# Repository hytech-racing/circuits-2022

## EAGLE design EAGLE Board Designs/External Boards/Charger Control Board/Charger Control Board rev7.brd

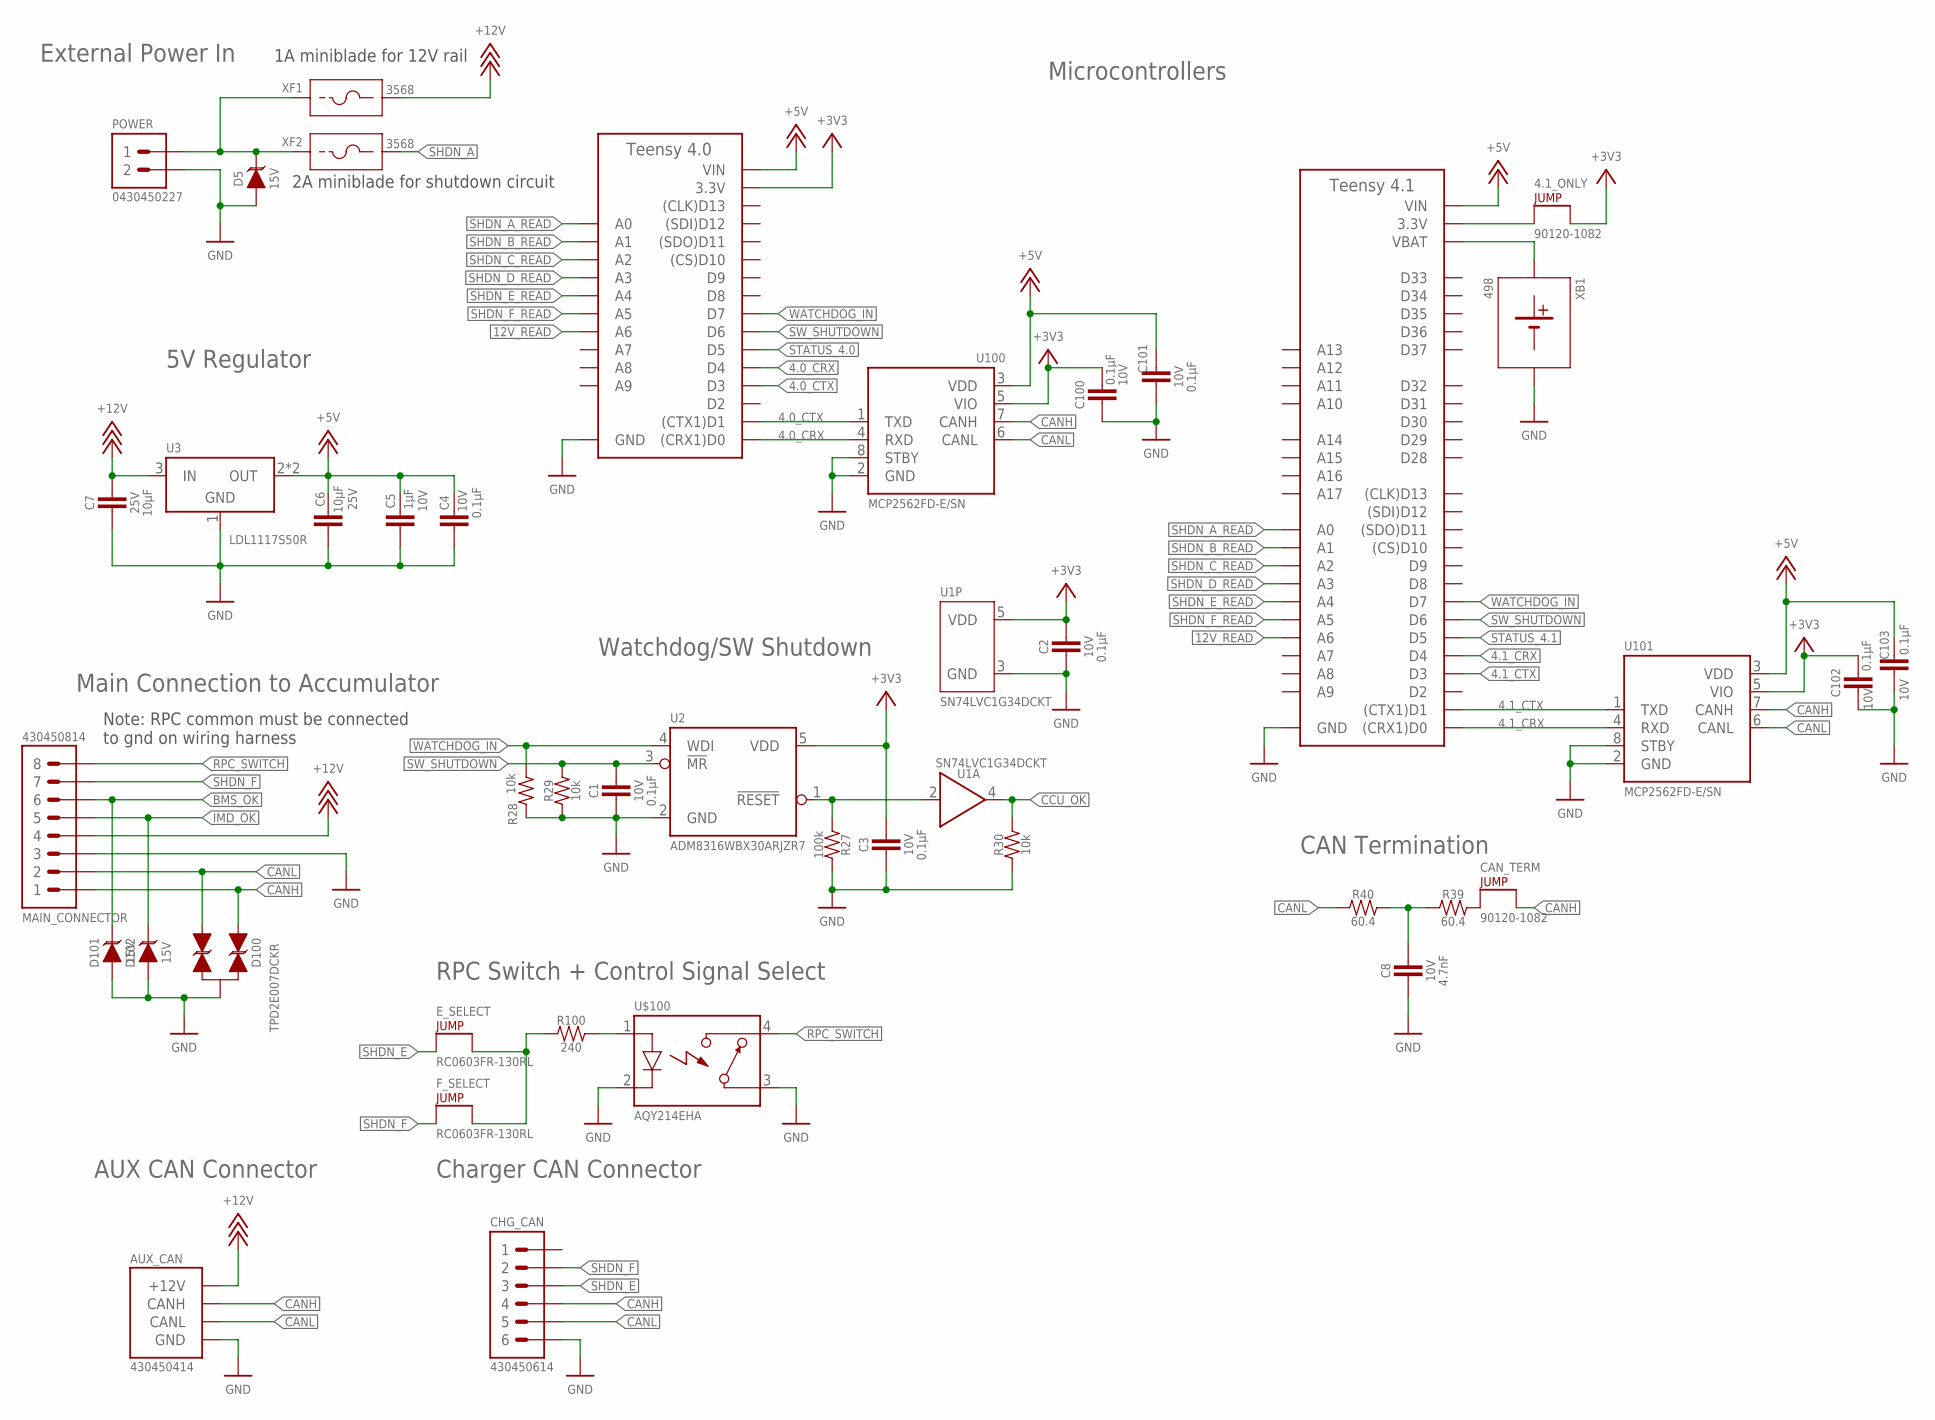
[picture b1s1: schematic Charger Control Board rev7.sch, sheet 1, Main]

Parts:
4.1_ONLY: JUMPER__1X02; 1X02
A1: TEENSY_4.1; TEENSY_LONG_EXT
A2: TEENSY_4.0; TEENSY_SHORT
AUX_CAN: CONNECTOR-CAN_MF_T_V_; MOLEX_MICROFIT_PTH_VERTICAL_04_DUAL
C1, C2, C3, C4, C100, C101, C102, C103: CAPACITOR_0603_10V_0.1UF; 0603-CAP
C5: CAPACITOR_0603_10V_1UF; 0603-CAP
C6, C7: CAPACITOR_0603_25V_10UF; 0603-CAP
C8: CAPACITOR_0603_10V_4.7NF; 0603-CAP
CAN_TERM: JUMPER__1X02; 1X02
CHG_CAN: CONNECTOR-6_MF_T_V_; MOLEX_MICROFIT_PTH_VERTICAL_06_DUAL
D5, D101, D102: TVS_15V; SOT-23
D100: TVS_BIDIRECTIONAL_DUAL; SC-70-3
E_SELECT: JUMPER_0603_; 0603-RES
F_SELECT: JUMPER_0603_; 0603-RES
MAIN_CONNECTOR: CONNECTOR-8_MF_T_V_; MOLEX_MICROFIT_PTH_VERTICAL_08_DUAL
POWER: CONNECTOR-2_μF_T_V_; MOLEX_MICROFIT_PTH_VERTICAL_02_DUAL
R27: RESISTOR_0603_100K; 0603-RES
R28, R29, R30: RESISTOR_0603_10K; 0603-RES
R39, R40: RESISTOR_0603_60.4; 0603-RES
R100: RESISTOR_0603_240; 0603-RES
U1: LOGICGATE_BUFFER; SC-70-5
U2: ADM8316WBX30; SOT-23-5
U3: VOLTAGE_REGULATOR_SOT-223_5V; SOT-223
U100, U101: MCP2562FD; SOIC-08(NARROW,0.15")
U$100: RELAY_SOLIDSTATE_NO; DIP-4
XB1: BATTERY_HOLDER_KEYSTONE_498; 498
XF1, XF2: FUSE_HOLDER_MINIBLADEPTH; 3568

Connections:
4.0_CRX: A2.D0 ((CRX1)D0), A2.D4, U100.4 (RXD)
4.0_CTX: A2.D1 ((CTX1)D1), A2.D3, U100.1 (TXD)
4.1_CRX: A1.D0 ((CRX1)D0), A1.D4, U101.4 (RXD)
4.1_CTX: A1.D1 ((CTX1)D1), A1.D3, U101.1 (TXD)
12V_READ: A1.D20 (A6), A2.D20 (A6); also elsewhere on the board
+3V3: 4.1_ONLY.2, A2.3.3V, C2.2, C3.2, C100.2, C102.2, U1.5 (VDD), U2.5 (VDD), U100.5 (VIO), U101.5 (VIO); also elsewhere on the board
+5V: A1.VIN, A2.VIN, C4.2, C5.1, C6.1, C101.2, C103.2, U3.2 (OUT), U3.4 (OUT), U100.3 (VDD), U101.3 (VDD); also elsewhere on the board
+12V: AUX_CAN.1 (+12V), C7.1, MAIN_CONNECTOR.4, U3.3 (IN), XF1.3 (2), XF1.4 (2); also elsewhere on the board
BMS_OK: D101.3 (C), MAIN_CONNECTOR.6; also elsewhere on the board
CANH: AUX_CAN.4 (CANH), CAN_TERM.2, CHG_CAN.4, D100.1 (C1), MAIN_CONNECTOR.1, U100.7 (CANH), U101.7 (CANH)
CANL: AUX_CAN.3 (CANL), CHG_CAN.5, D100.2 (C2), MAIN_CONNECTOR.2, R40.1, U100.6 (CANL), U101.6 (CANL)
CCU_OK: R30.2, U1.4 (OUT); also elsewhere on the board
GND: A1.AGND/GND (GND), A1.GND, A1.GND@2 (GND), A2.AGND/GND (GND), A2.GND, AUX_CAN.2 (GND), C1.1, C2.1, C3.1, C4.1, C5.2, C6.2, C7.2, C8.2, C100.1, C101.1, C102.1, C103.1, CHG_CAN.6, D5.1 (A), D100.3 (A), D101.1 (A), D102.1 (A), MAIN_CONNECTOR.3, POWER.2, R27.2, R28.2, R29.1, R30.1, U1.3 (GND), U2.2 (GND), U3.1 (GND), U100.2 (GND), U100.8 (STBY), U101.2 (GND), U101.8 (STBY), U$100.2 (CONTROL-), U$100.3 (CONTACT1), XB1.2 (MINUS); also elsewhere on the board
IMD_OK: D102.3 (C), MAIN_CONNECTOR.5; also elsewhere on the board
unnamed: D5.3 (C), POWER.1, XF1.1, XF1.2 (1), XF2.1, XF2.2 (1)
unnamed: R27.1, U1.2 (IN), U2.1 (!RESET!)
unnamed: CAN_TERM.1, R39.2
unnamed: E_SELECT.2, F_SELECT.2, R100.1
unnamed: A1.VBAT, XB1.1 (PLUS)
unnamed: C8.1, R39.1, R40.2
unnamed: R100.2, U$100.1 (CONTROL+)
unnamed: 4.1_ONLY.1, A1.3V3 (3.3V), A1.3V3@2 (3.3V), A1.3V3@3 (3.3V)
RPC_SWITCH: MAIN_CONNECTOR.8, U$100.4 (CONTACT2)
SHDN_A: XF2.3 (2), XF2.4 (2); also elsewhere on the board
SHDN_A_READ: A1.D14 (A0), A2.D14 (A0); also elsewhere on the board
SHDN_B_READ: A1.D15 (A1), A2.D15 (A1); also elsewhere on the board
SHDN_C_READ: A1.D16 (A2), A2.D16 (A2); also elsewhere on the board
SHDN_D_READ: A1.D17 (A3), A2.D17 (A3); also elsewhere on the board
SHDN_E: CHG_CAN.3, E_SELECT.1; also elsewhere on the board
SHDN_E_READ: A1.D18 (A4), A2.D18 (A4); also elsewhere on the board
SHDN_F: CHG_CAN.1, CHG_CAN.2, F_SELECT.1, MAIN_CONNECTOR.7; also elsewhere on the board
SHDN_F_READ: A1.D19 (A5), A2.D19 (A5); also elsewhere on the board
STATUS_4.0: A2.D5; also elsewhere on the board
STATUS_4.1: A1.D5; also elsewhere on the board
SW_SHUTDOWN: A1.D6, A2.D6, C1.2, R29.2, U2.3 (!MR!)
WATCHDOG_IN: A1.D7, A2.D7, R28.1, U2.4 (WDI)

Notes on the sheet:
External Power In
5V Regulator
Main Connection to Accumulator
CAN Termination
Microcontrollers
Watchdog/SW Shutdown
Charger CAN Connector
AUX CAN Connector
1A miniblade for 12V rail
2A miniblade for shutdown circuit
RPC Switch + Control Signal Select
Note: RPC common must be connected to gnd on wiring harness

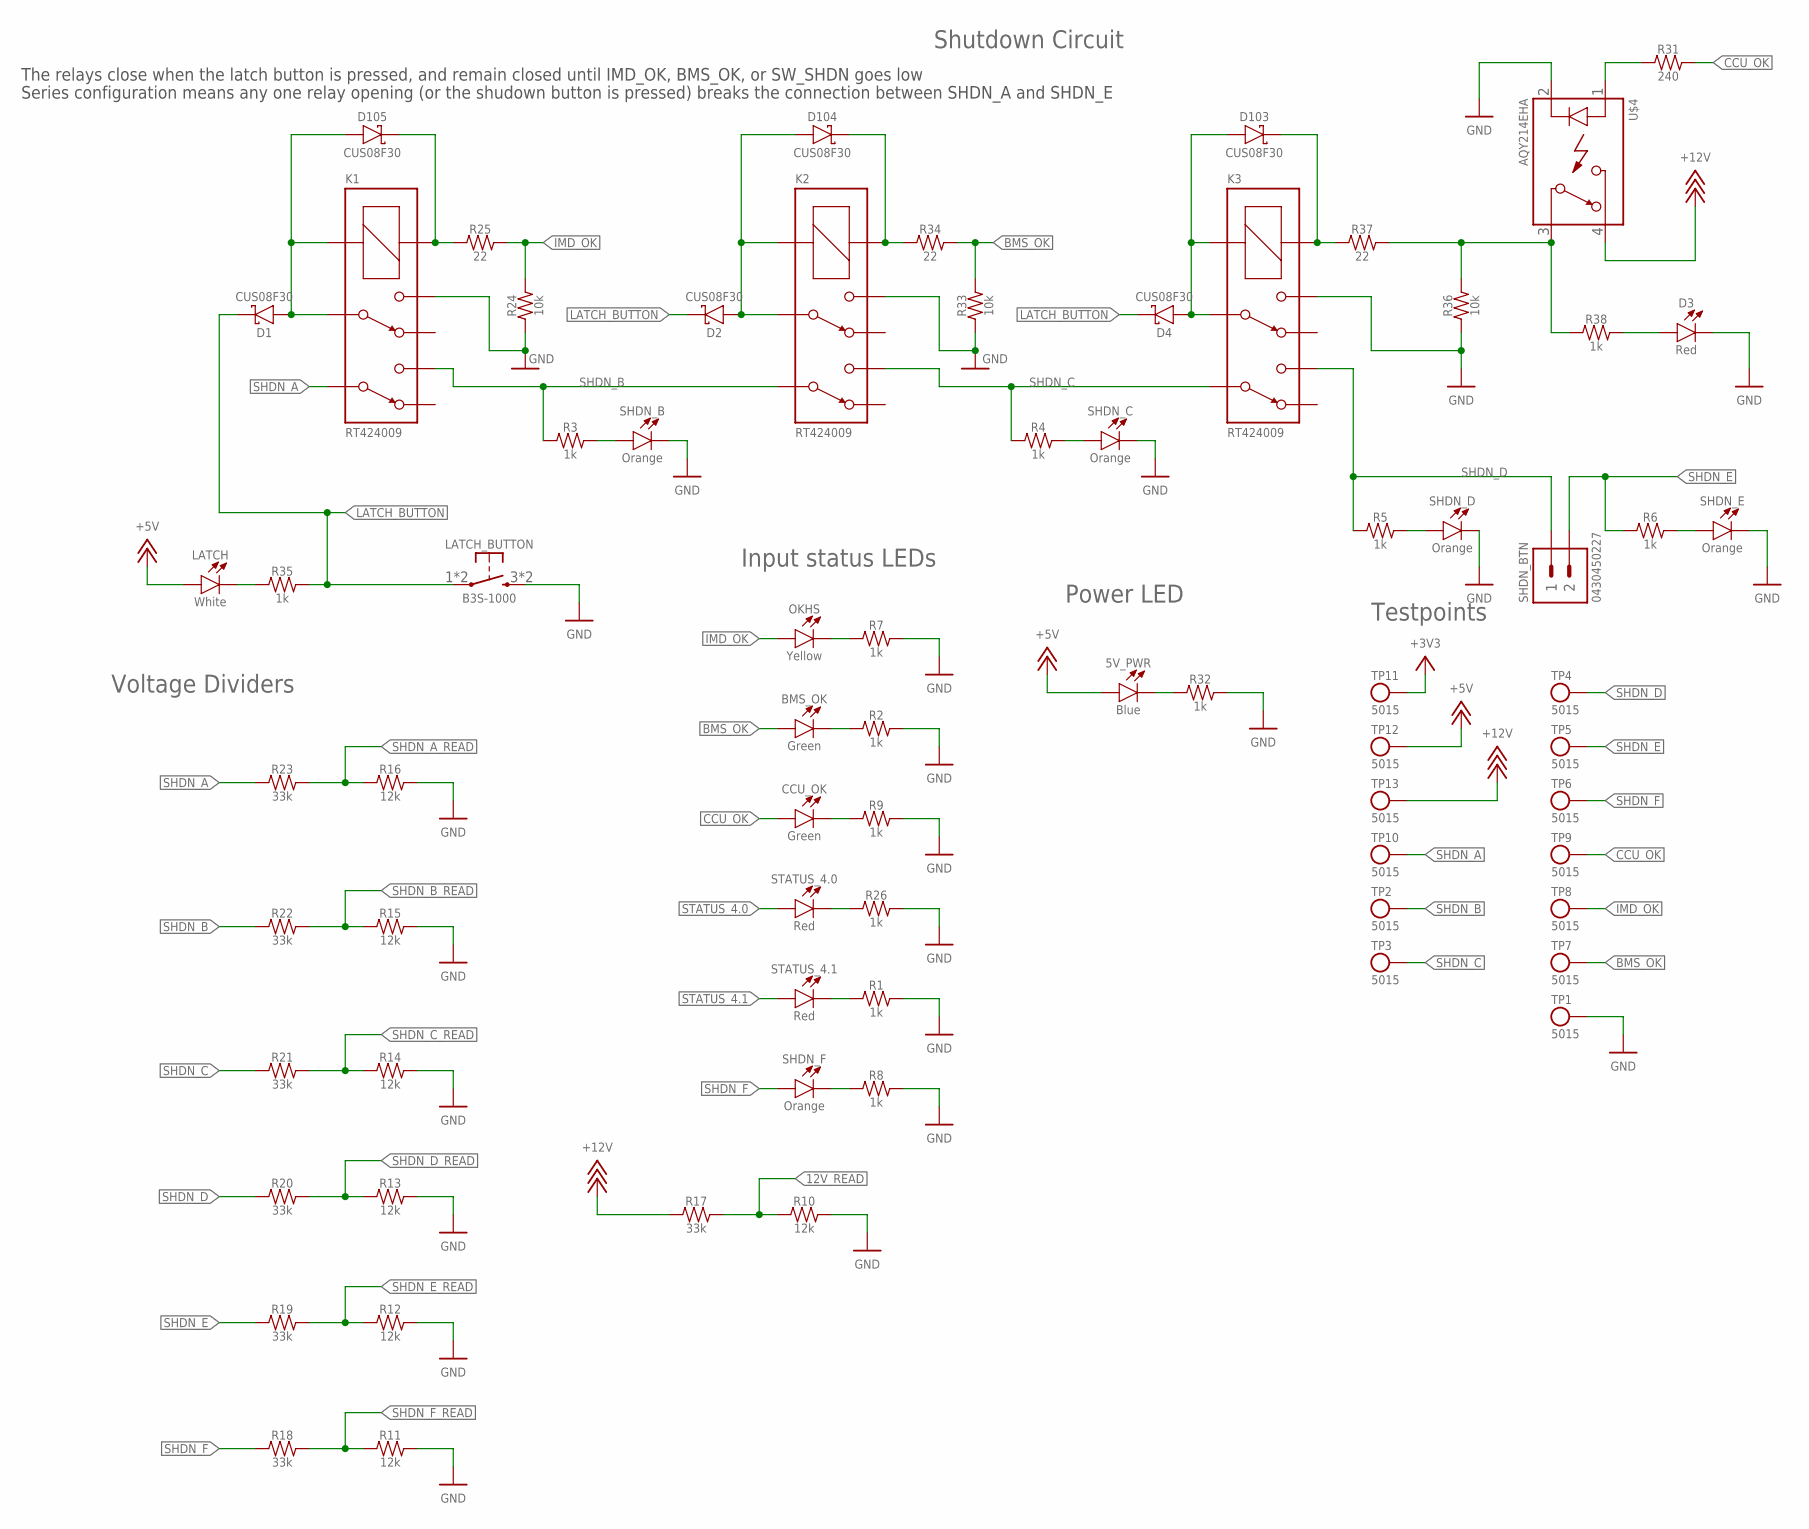
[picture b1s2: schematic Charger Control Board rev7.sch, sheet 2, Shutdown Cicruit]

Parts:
5V_PWR: LED_0603_BLUE; 0603-LED
BMS_OK: LED_0603_GREEN; 0603-LED
CCU_OK: LED_0603_GREEN; 0603-LED
D1, D2, D4, D103, D104, D105: SCHOTTKY_SOD323_30V; SOD-323
D3: LED_0603_RED; 0603-LED
K1, K2, K3: RELAY_DPDT; RT*2*
LATCH: LED_0603_WHITE; 0603-LED
LATCH_BUTTON: BUTTON; B3S-100X
OKHS: LED_0603_YELLOW; 0603-LED
R1, R2, R3, R4, R5, R6, R7, R8, R9, R26, R32, R35, R38: RESISTOR_0603_1K; 0603-RES
R10, R11, R12, R13, R14, R15, R16: RESISTOR_0603_12K; 0603-RES
R17, R18, R19, R20, R21, R22, R23: RESISTOR_0603_33K; 0603-RES
R24, R33, R36: RESISTOR_0603_10K; 0603-RES
R25, R34, R37: RESISTOR_0603_22; 0603-RES
R31: RESISTOR_0603_240; 0603-RES
SHDN_B: LED_0603_ORANGE; 0603-LED
SHDN_BTN: CONNECTOR-2_μF_T_V_; MOLEX_MICROFIT_PTH_VERTICAL_02_DUAL
SHDN_C: LED_0603_ORANGE; 0603-LED
SHDN_D: LED_0603_ORANGE; 0603-LED
SHDN_E: LED_0603_ORANGE; 0603-LED
SHDN_F: LED_0603_ORANGE; 0603-LED
STATUS_4.0, STATUS_4.1: LED_0603_RED; 0603-LED
TP1, TP2, TP3, TP4, TP5, TP6, TP7, TP8, TP9, TP10, TP11, TP12, TP13: TEST_POINT; 5015
U$4: RELAY_SOLIDSTATE_NO; DIP-4

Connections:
12V_READ: R10.1, R17.2; also elsewhere on the board
+3V3: TP11.1; also elsewhere on the board
+5V: 5V_PWR.2 (A), LATCH.2 (A), TP12.1; also elsewhere on the board
+12V: R17.1, TP13.1, U$4.4 (CONTACT2); also elsewhere on the board
BMS_OK: BMS_OK.2 (A), R33.2, R34.2, TP7.1; also elsewhere on the board
CCU_OK: CCU_OK.2 (A), R31.2, TP9.1; also elsewhere on the board
GND: D3.1 (C), K1.14 (4), K2.14 (4), K3.14 (4), LATCH_BUTTON.3 (S), LATCH_BUTTON.4 (S), R1.2, R2.2, R7.2, R8.2, R9.2, R10.2, R11.2, R12.2, R13.2, R14.2, R15.2, R16.2, R24.1, R26.2, R32.2, R33.1, R36.1, SHDN_B.1 (C), SHDN_C.1 (C), SHDN_D.1 (C), SHDN_E.1 (C), TP1.1, U$4.2 (CONTROL-); also elsewhere on the board
IMD_OK: OKHS.2 (A), R24.2, R25.2, TP8.1; also elsewhere on the board
LATCH_BUTTON: D1.C, D2.C, D4.C, LATCH_BUTTON.1, LATCH_BUTTON.2, R35.2
unnamed: R8.1, SHDN_F.1 (C)
unnamed: R31.1, U$4.1 (CONTROL+)
unnamed: D1.A, D105.A, K1.11 (3), K1.A2 (COIL-)
unnamed: D105.C, K1.A1 (COIL+), R25.1
unnamed: D104.C, K2.A1 (COIL+), R34.1
unnamed: D2.A, D104.A, K2.11 (3), K2.A2 (COIL-)
unnamed: D103.C, K3.A1 (COIL+), R37.1
unnamed: R36.2, R37.2, R38.1, U$4.3 (CONTACT1)
unnamed: LATCH.1 (C), R35.1
unnamed: R5.2, SHDN_D.2 (A)
unnamed: R6.2, SHDN_E.2 (A)
unnamed: D4.A, D103.A, K3.11 (3), K3.A2 (COIL-)
unnamed: D3.2 (A), R38.2
unnamed: R4.2, SHDN_C.2 (A)
unnamed: R3.2, SHDN_B.2 (A)
unnamed: OKHS.1 (C), R7.1
unnamed: BMS_OK.1 (C), R2.1
unnamed: CCU_OK.1 (C), R9.1
unnamed: R26.1, STATUS_4.0.1 (C)
unnamed: 5V_PWR.1 (C), R32.1
unnamed: R1.1, STATUS_4.1.1 (C)
SHDN_A: K1.21 (6), R23.1, TP10.1; also elsewhere on the board
SHDN_A_READ: R16.1, R23.2; also elsewhere on the board
SHDN_B: K1.24 (5), K2.21 (6), R3.1, R22.1, TP2.1
SHDN_B_READ: R15.1, R22.2; also elsewhere on the board
SHDN_C: K2.24 (5), K3.21 (6), R4.1, R21.1, TP3.1
SHDN_C_READ: R14.1, R21.2; also elsewhere on the board
SHDN_D: K3.24 (5), R5.1, R20.1, SHDN_BTN.1, TP4.1
SHDN_D_READ: R13.1, R20.2; also elsewhere on the board
SHDN_E: R6.1, R19.1, SHDN_BTN.2, TP5.1; also elsewhere on the board
SHDN_E_READ: R12.1, R19.2; also elsewhere on the board
SHDN_F: R18.1, SHDN_F.2 (A), TP6.1; also elsewhere on the board
SHDN_F_READ: R11.1, R18.2; also elsewhere on the board
STATUS_4.0: STATUS_4.0.2 (A); also elsewhere on the board
STATUS_4.1: STATUS_4.1.2 (A); also elsewhere on the board

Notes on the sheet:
Input status LEDs
Power LED
Voltage Dividers
Shutdown Circuit
Testpoints
The relays close when the latch button is pressed, and remain closed until IMD_OK, BMS_OK, or SW_SHDN goes low
Series configuration means any one relay opening (or the shudown button is pressed) breaks the connection between SHDN_A and SHDN_E

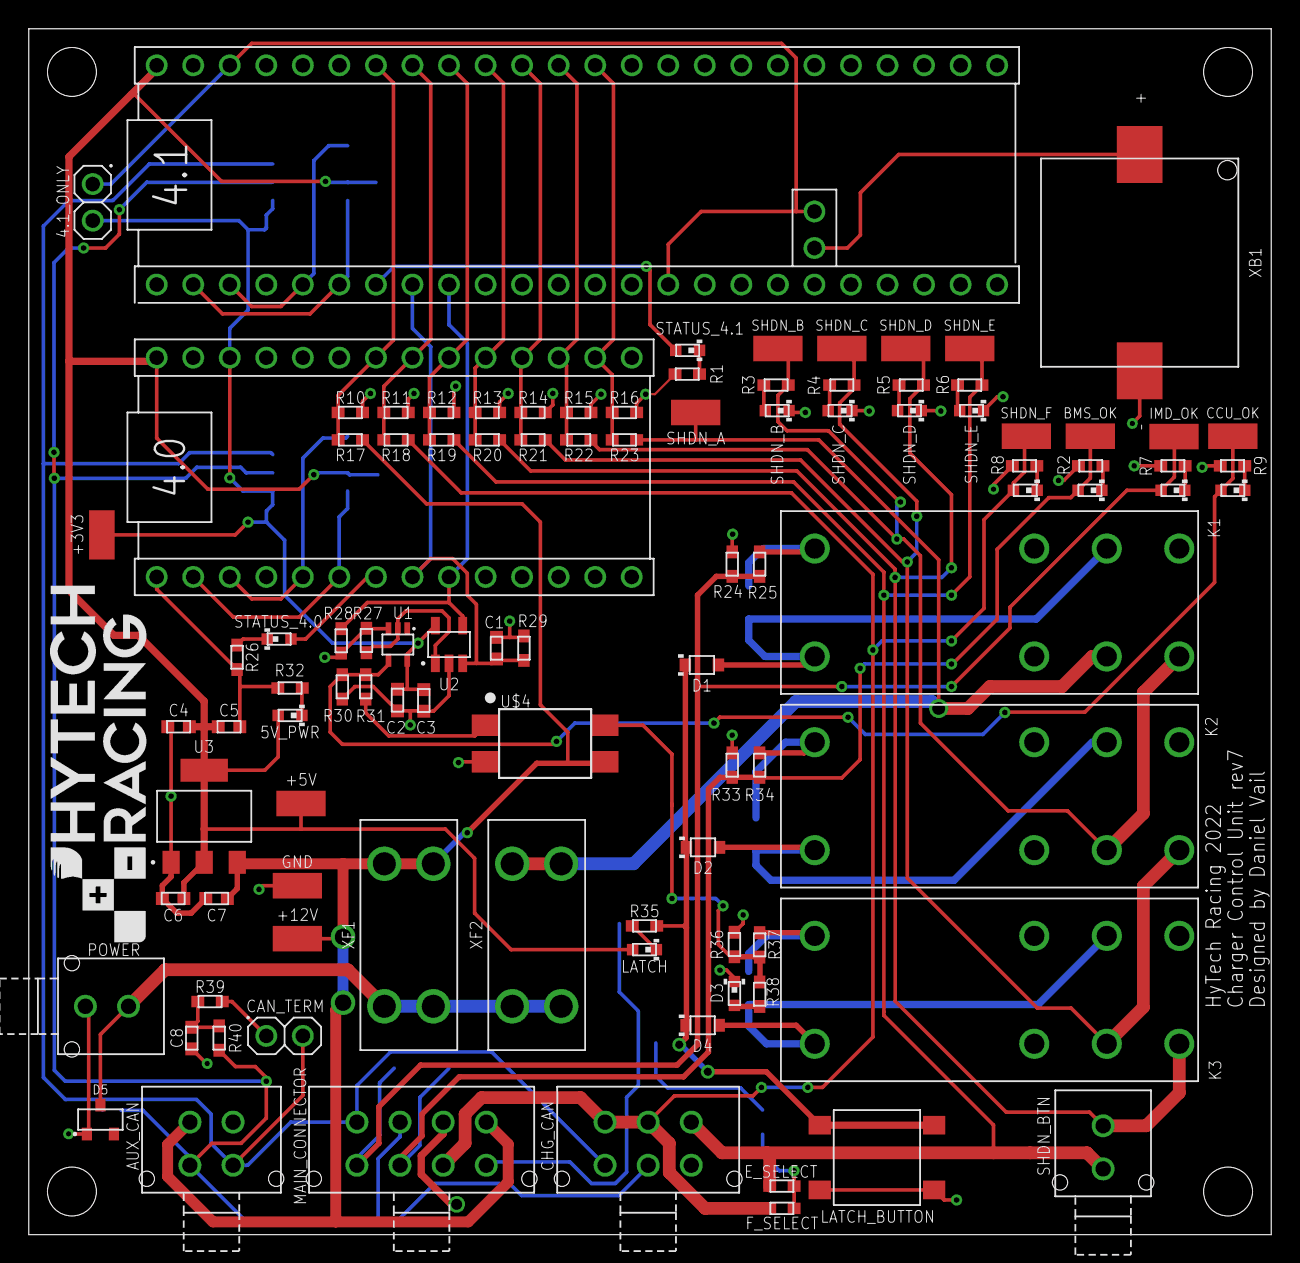
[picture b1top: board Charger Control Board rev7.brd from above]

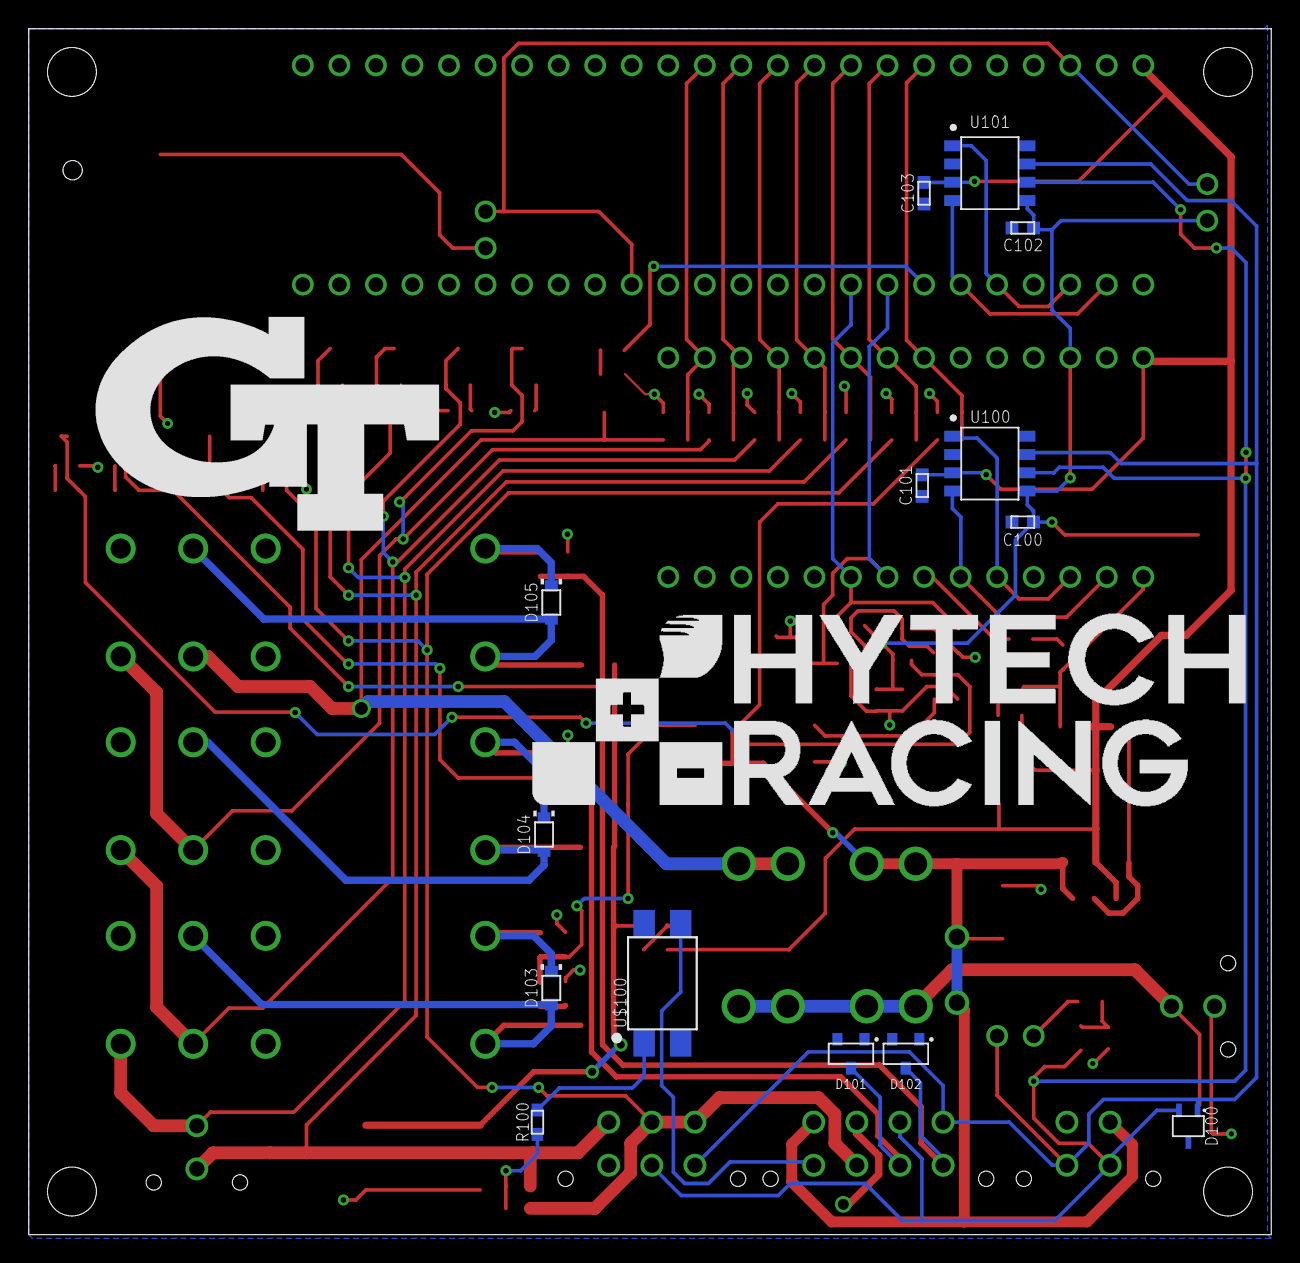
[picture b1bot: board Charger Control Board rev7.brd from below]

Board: 2 copper layers, 86.4 x 83.8 mm, 121 parts (16 on the bottom side), 61 nets.

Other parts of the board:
U$1, U$2, U$6, U$7: MOUNTING_M3
U$5: LOGO_HYTECH_MEDIUM
U$9: LOGO_HYTECH_LARGE
U$10: LOGO_GT_LARGE

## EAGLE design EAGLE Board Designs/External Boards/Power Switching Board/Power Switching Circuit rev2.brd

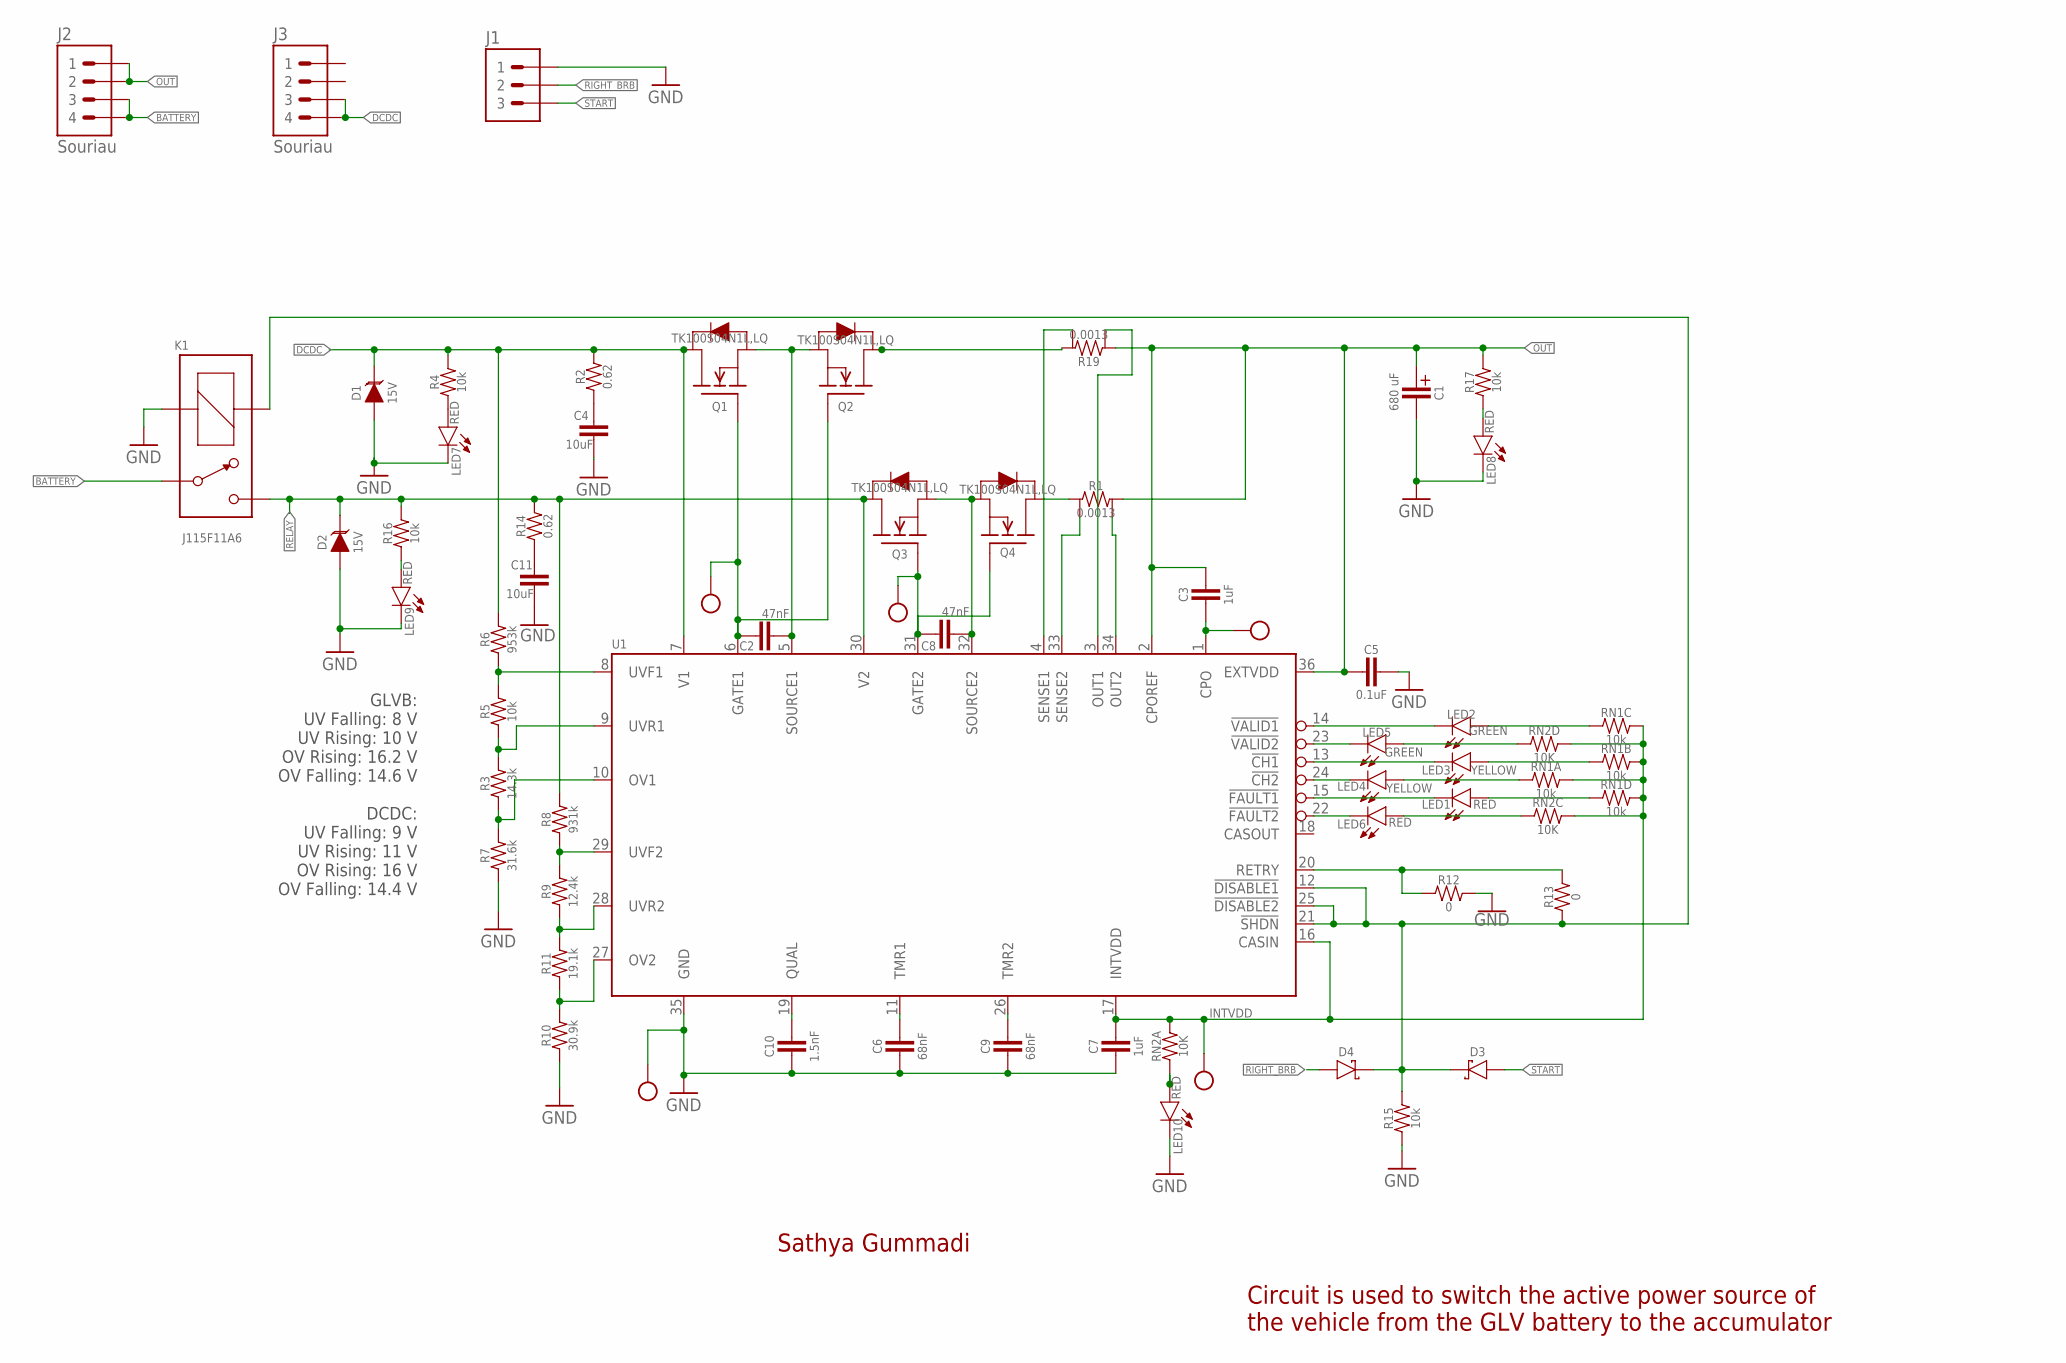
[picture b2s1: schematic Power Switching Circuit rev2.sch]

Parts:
C1: CAPACITOR_POLARIZED; EEE-FK1H681AM
C2, C8: 47nF; 0603-CAP@1
C3, C7: 1uF; 0805
C4, C11: 10uF; 1206-CAP
C5: 0.1uF; 0603-CAP@1
C6, C9: 68nF; 0603-CAP@1
C10: 1.5nF; 0603-CAP@1
D1, D2: TVS_15V; SOT-23
D3, D4: SCHOTTKY; CLP1608-2L
J1: CONNECTOR-3_; SOURIAU_04-35
J2, J3: CONNECTOR-4_SOURIAU_; SOURIAU_12-04
K1: J115F11A6; J115F11A*6*
LED1, LED6, LED7, LED8, LED9, LED10: RED; LED-603
LED2, LED5: GREEN; LED-603
LED3, LED4: YELLOW; LED-603
Q1, Q2, Q3, Q4: TRANSISTOR_N_MOS_2-7K1S_TK100S04N1L,LQ; DPAK(2-7K1S)
R1, R19: RESISTOR_SENSE; WSL2726
R2, R14: 0.62; 0805
R3: 14.3k; 0603-RES
R4, R5, R15, R16, R17: 10k; 0603-RES
R6: 953k; 0603-RES
R7: 31.6k; 0603-RES
R8: 931k; 0603-RES
R9: 12.4k; 0603-RES
R10: 30.9k; 0603-RES
R11: 19.1k; 0603-RES
R12, R13: 0; 0603-RES
RN1: RESISTOR_NETWORK_4_10K; YC/TC164
RN2: RESISTOR_NETWORK_4_10K; 1206-RES
U1: LTC4421; SSOP-36
U$7, U$8, U$9, U$10, U$11: TEST_POINTMICRO_MINIATURE; MICRO_MINIATURE

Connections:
!CH1: LED3.C, U1.13 (!CH1)
!CH2: LED4.C, U1.24 (!CH2)
!FAULT1: LED1.C, U1.15 (!FAULT1)
!FAULT2: LED6.C, U1.22 (!FAULT2)
!SHDN!: D3.2 (C), D4.2 (C), K1.COIL1 (COIL+), R13.1, R15.2, U1.12 (!DISABLE1), U1.21 (!SHDN), U1.25 (!DISABLE2)
!VALID1: LED2.C, U1.14 (!VALID1)
!VALID2: LED5.C, U1.23 (!VALID2)
BATTERY: J2.3, J2.4, K1.CONTACT1
CPO: C3.2, U1.1 (CPO), U$9.P$1
DCDC: D1.3 (C), J3.3, J3.4, Q1.2 (D), R2.2, R4.2, R6.2, U1.7 (V1)
GATE1: C2.2, Q1.1 (G), Q2.1 (G), U1.6 (GATE1), U$10.P$1
GATE2: C8.2, Q3.1 (G), Q4.1 (G), U1.31 (GATE2), U$7.P$1
GND: C1.P$2 (MINUS), C4.2, C5.1, C6.2, C7.2, C9.2, C10.2, C11.2, D1.1 (A), D2.1 (A), J1.A (1), K1.COIL2 (COIL-), LED7.C, LED8.C, LED9.C, LED10.C, R7.1, R10.1, R12.2, R15.1, U1.35 (GND), U$11.P$1
INTVDD: C7.1, RN1.5 (2), RN1.6 (2), RN1.7 (2), RN1.8 (2), RN2.5 (2), RN2.6 (2), RN2.8 (2), U1.16 (CASIN), U1.17 (INTVDD), U$8.P$1
unnamed: C10.1, U1.19 (QUAL)
unnamed: C6.1, U1.11 (TMR1)
unnamed: C9.1, U1.26 (TMR2)
unnamed: C11.1, R14.1
unnamed: Q4.2 (D), R1.1
unnamed: LED9.A, R16.1
unnamed: LED7.A, R4.1
unnamed: Q2.2 (D), R19.2
unnamed: LED10.A, RN2.1
unnamed: LED8.A, R17.1
unnamed: LED6.A, RN2.3 (1)
unnamed: LED1.A, RN1.4 (1)
unnamed: LED4.A, RN1.1
unnamed: LED3.A, RN1.2 (1)
unnamed: LED5.A, RN2.4 (1)
unnamed: LED2.A, RN1.3 (1)
unnamed: C4.1, R2.1
OUT: C1.P$1 (PLUS), C3.1, C5.2, J2.1, J2.2, R1.2, R17.2, R19.1, U1.2 (CPOREF), U1.36 (EXTVDD)
OUT1: R19.3, U1.3 (OUT1)
OUT2: R1.4, U1.34 (OUT2)
OV1: R3.1, R7.2, U1.10 (OV1)
OV2: R10.2, R11.1, U1.27 (OV2)
RELAY: D2.3 (C), K1.CONTACT2 (S), Q3.2 (D), R8.2, R14.2, R16.2, U1.30 (V2)
RETRY: R12.1, R13.2, U1.20 (RETRY)
RIGHT_BRB: D4.1 (A), J1.B (2)
SENSE: R19.4, U1.4 (SENSE1)
SENSE2: R1.3, U1.33 (SENSE2)
SOURCE1: C2.1, Q1.3 (S), Q2.3 (S), U1.5 (SOURCE1)
SOURCE2: C8.1, Q3.3 (S), Q4.3 (S), U1.32 (SOURCE2)
START: D3.1 (A), J1.C (3)
UVF1: R5.2, R6.1, U1.8 (UVF1)
UVF2: R8.1, R9.2, U1.29 (UVF2)
UVR1: R3.2, R5.1, U1.9 (UVR1)
UVR2: R9.1, R11.2, U1.28 (UVR2)

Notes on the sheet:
Sathya Gummadi
Circuit is used to switch the active power source of the vehicle from the GLV battery to the accumulator
GLVB: UV Falling: 8 V UV Rising: 10 V OV Rising: 16.2 V OV Falling: 14.6 V DCDC: UV Falling: 9 V UV Rising: 11 V OV Rising: 16 V OV Falling: 14.4 V
680 uF

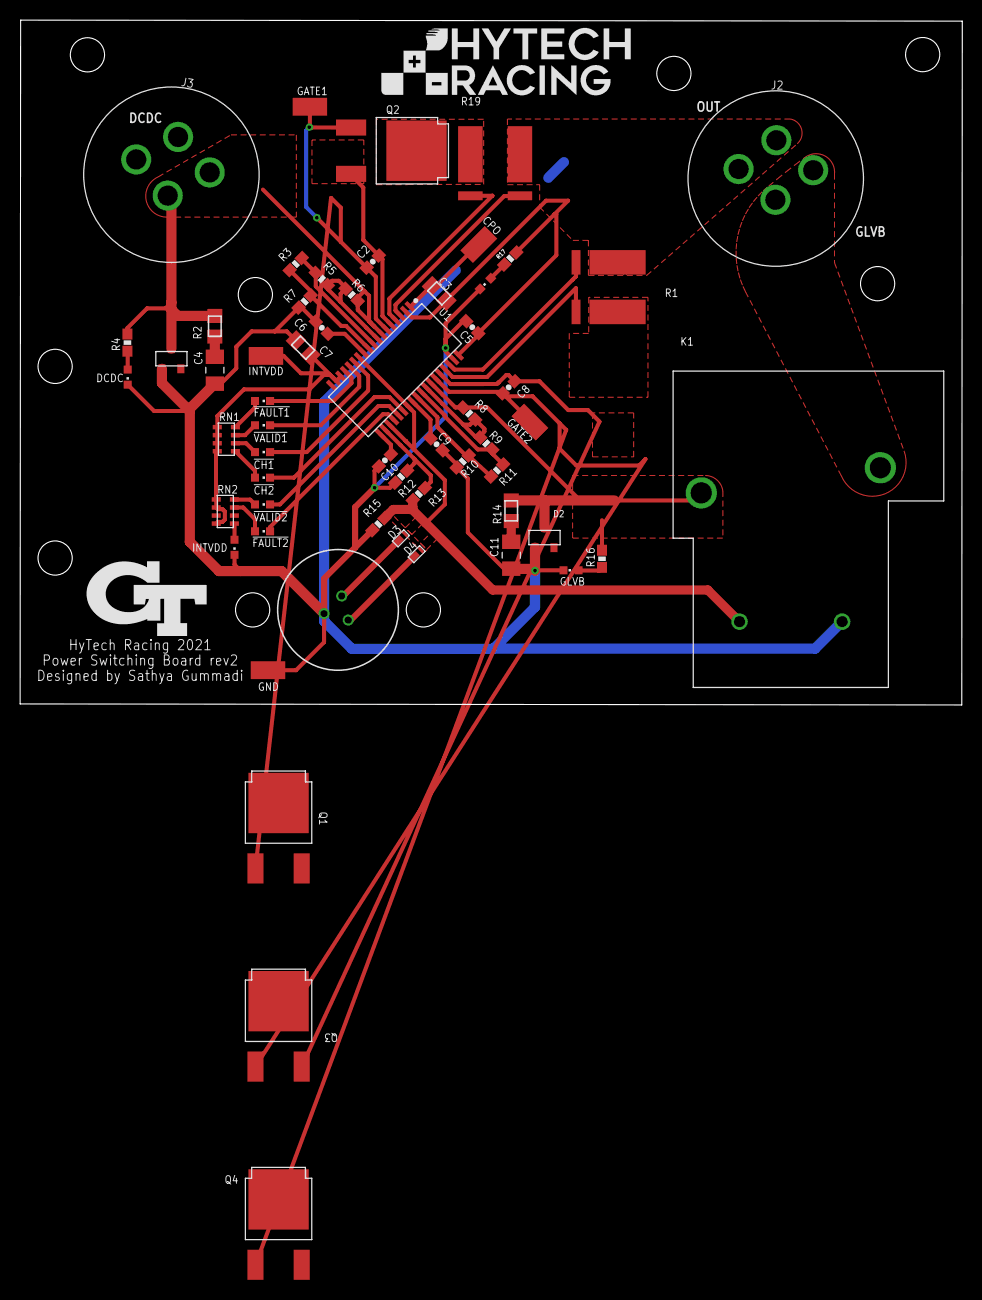
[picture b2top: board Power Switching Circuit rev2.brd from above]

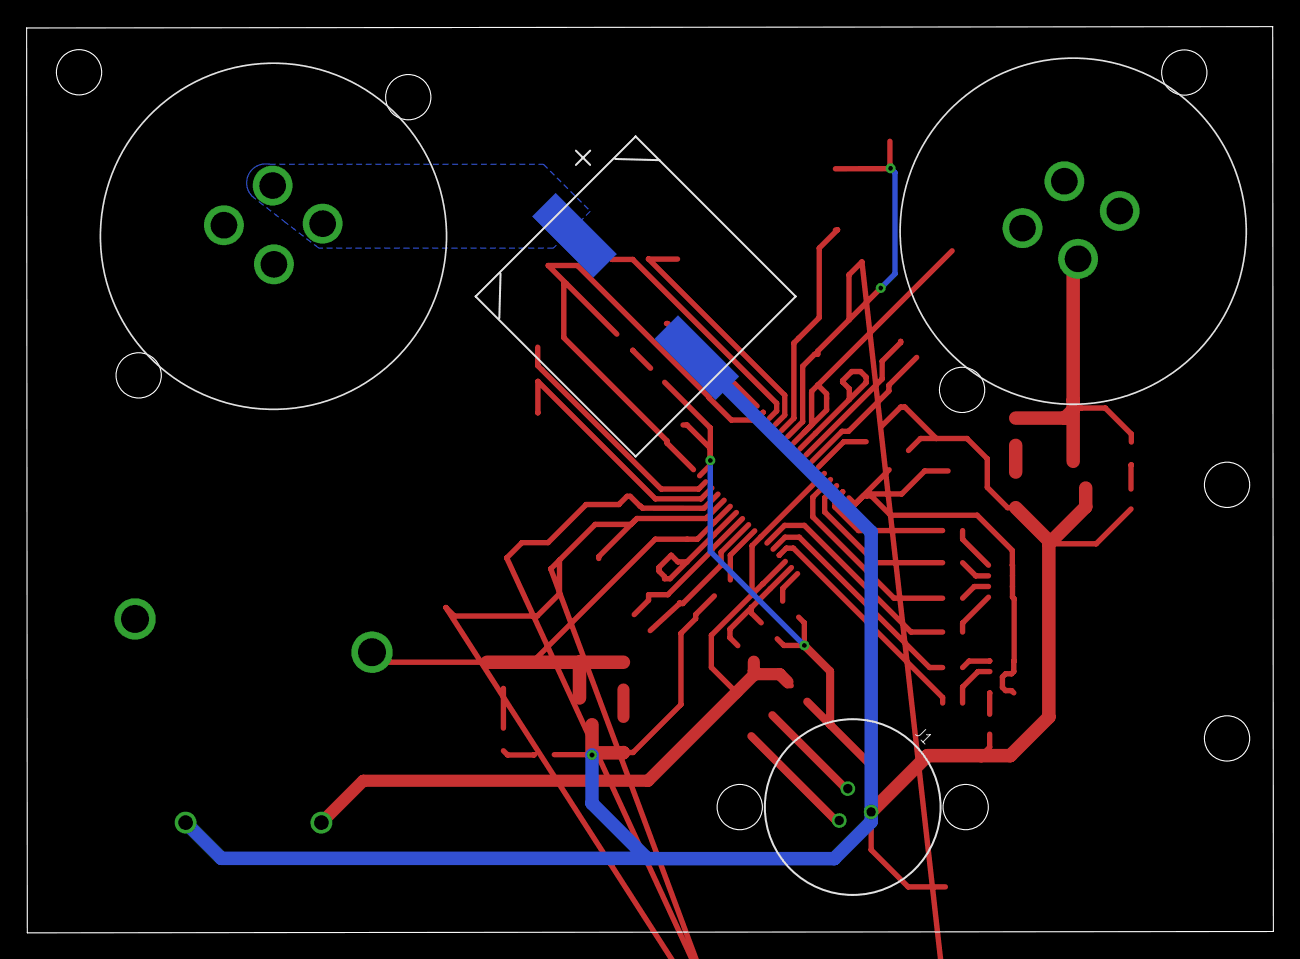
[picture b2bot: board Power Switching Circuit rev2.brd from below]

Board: 2 copper layers, 93.6 x 68.1 mm, 64 parts (4 on the bottom side), 48 nets.

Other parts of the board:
U$1, U$3, U$4: MOUNTING_M3
U$5: LOGO_GT_0.50"
U$6: LOGO_HYTECH_1.0"
